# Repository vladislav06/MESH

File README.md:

# DSAN
Distributed Sensor Actuator Network

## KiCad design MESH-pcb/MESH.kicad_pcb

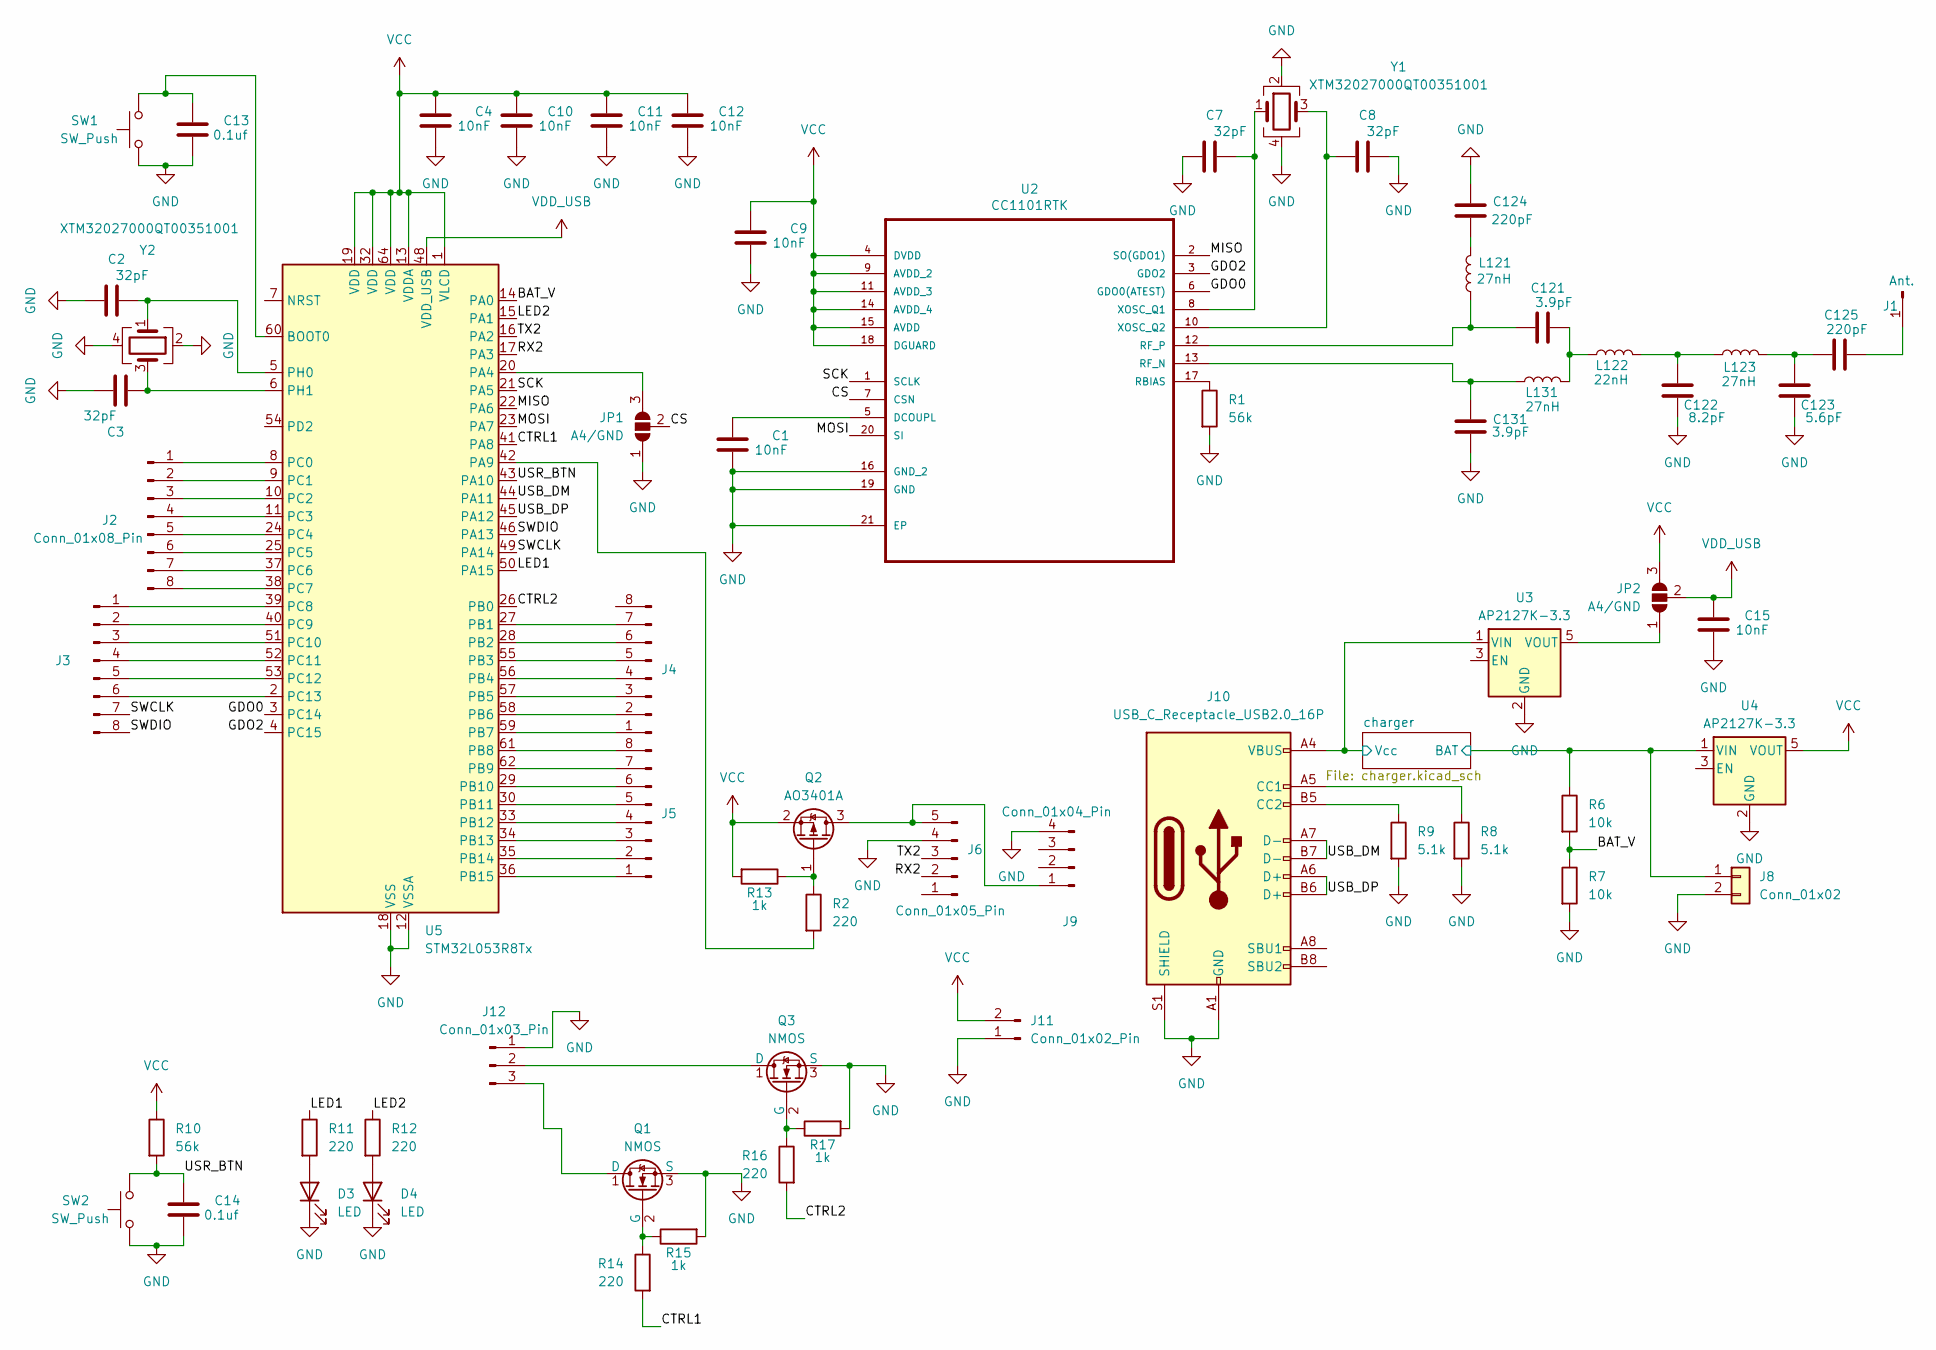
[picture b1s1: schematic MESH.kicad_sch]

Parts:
C1, C4, C9, C10, C11, C12, C15: 10nF; C_0402_1005Metric
C2, C3, C7, C8: 32pF; C_0402_1005Metric
C13, C14: 0.1uf; C_0402_1005Metric
C121, C131: 3.9pF; C_0402_1005Metric
C122: 8.2pF; C_0402_1005Metric
C123: 5.6pF; C_0402_1005Metric
C124, C125: 220pF; C_0402_1005Metric
D3, D4: LED; LED_0603_1608Metric_Pad1.05x0.95mm_HandSolder
J1: Ant.; PinHeader_1x01_P1.00mm_Vertical
J2, J3, J4, J5: Conn_01x08_Pin; PinHeader_1x08_P2.54mm_Bare
J6: Conn_01x05_Pin; PinHeader_1x05_P1.00mm_Vertical
J8: Conn_01x02; PinHeader_1x02_P2.54mm_Vertical
J9: Conn_01x04_Pin; PinHeader_1x04_P2.00mm_Vertical
J10: USB_C_Receptacle_USB2.0_16P; USB_C_Receptacle_Palconn_UTC16-G
J11: Conn_01x02_Pin; PinHeader_1x02_P2.54mm_Bare
J12: Conn_01x03_Pin; PinHeader_1x03_P2.54mm_Bare
JP1, JP2: A4/GND; SolderJumper-3_P2.0mm_Open_TrianglePad1.0x1.5mm_NumberLabels
L121, L123, L131: 27nH; L_0402_1005Metric
L122: 22nH; L_0402_1005Metric
Q1, Q3: NMOS; SOIC127P600X175-8N
Q2: AO3401A; SOT-23
R1, R10: 56k; R_0201_0603Metric_Pad0.64x0.40mm_HandSolder
R2, R11, R12, R14, R16: 220; R_0201_0603Metric_Pad0.64x0.40mm_HandSolder
R6, R7: 10k; R_0201_0603Metric_Pad0.64x0.40mm_HandSolder
R8, R9: 5.1k; R_0201_0603Metric_Pad0.64x0.40mm_HandSolder
R13, R15, R17: 1k; R_0201_0603Metric_Pad0.64x0.40mm_HandSolder
SW1, SW2: SW_Push; SW_5.6_3.1
U2: CC1101RTK; QFN-20-1EP_4x4mm_P0.5mm_EP2.5x2.5mm
U3, U4: AP2127K-3.3; SOT-23-5
U5: STM32L053R8Tx; LQFP-64_10x10mm_P0.5mm
Y1, Y2: XTM32027000QT00351001; Crystal_SMD_3225-4Pin_3.2x2.5mm_HandSoldering

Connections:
/BAT_V: R6.2, R7.1, U5.14 (PA0)
/CS: JP1.2 (C), U2.7 (CSN)
/CTRL1: R14.2, U5.41 (PA8)
/CTRL2: R16.2, U5.26 (PB0)
/GDO0: U2.6 (GDO0(ATEST)), U5.3 (PC14)
/GDO2: U2.3 (GDO2), U5.4 (PC15)
/LED1: R11.1, U5.50 (PA15)
/LED2: R12.1, U5.15 (PA1)
/MISO: U2.2 (SO(GDO1)), U5.22 (PA6)
/MOSI: U2.20 (SI), U5.23 (PA7)
/RX2: J6.2, U5.17 (PA3)
/SCK: U2.1 (SCLK), U5.21 (PA5)
/SWCLK: J3.7, U5.49 (PA14)
/SWDIO: J3.8, U5.46 (PA13)
/TX2: J6.3, U5.16 (PA2)
/USB_DM: J10.A7 (D-), J10.B7 (D-), U5.44 (PA11)
/USB_DP: J10.A6 (D+), J10.B6 (D+), U5.45 (PA12)
/USR_BTN: C14.1, R10.2, SW2.2, U5.43 (PA10)
/charger/BAT: J8.1, R6.1, U4.1 (VIN); also elsewhere on the board
/charger/Vcc: J10.A4 (VBUS), J10.A9 (VBUS), J10.B4 (VBUS), J10.B9 (VBUS), U3.1 (VIN); also elsewhere on the board
GND: C1.2, C2.1, C3.2, C4.2, C7.1, C8.2, C9.2, C10.2, C11.2, C12.2, C13.2, C14.2, C15.2, C122.2, C123.2, C124.1, C131.2, D3.1 (K), D4.1 (K), J6.4, J8.2, J9.4, J10.A1 (GND), J10.A12 (GND), J10.B1 (GND), J10.B12 (GND), J10.S1 (SHIELD), J11.1, J12.1, JP1.1 (A), Q1.3 (S), Q3.3 (S), R1.2, R7.2, R8.2, R9.2, R15.2, R17.2, SW1.1, SW2.1, U2.16 (GND_2), U2.19 (GND), U2.21 (EP), U3.2 (GND), U4.2 (GND), U5.12 (VSSA), U5.18 (VSS), U5.31 (VSS), U5.47 (VSS), U5.63 (VSS), Y1.2, Y1.4, Y2.2, Y2.4; also elsewhere on the board
unnamed: C121.2, L122.1, L131.2
unnamed: C122.1, L122.2, L123.1
unnamed: C123.1, C125.1, L123.2
unnamed: C124.2, L121.2
unnamed: D3.2 (A), R11.2
unnamed: D4.2 (A), R12.2
unnamed: C125.2, J1.1
unnamed: J2.1, U5.8 (PC0)
unnamed: J2.2, U5.9 (PC1)
unnamed: J2.3, U5.10 (PC2)
unnamed: J2.4, U5.11 (PC3)
unnamed: J2.5, U5.24 (PC4)
unnamed: J2.6, U5.25 (PC5)
unnamed: J2.7, U5.37 (PC6)
unnamed: J2.8, U5.38 (PC7)
unnamed: J3.1, U5.39 (PC8)
unnamed: J3.2, U5.40 (PC9)
unnamed: J3.3, U5.51 (PC10)
unnamed: J3.4, U5.52 (PC11)
unnamed: J3.5, U5.53 (PC12)
unnamed: J3.6, U5.2 (PC13)
unnamed: J4.1, U5.59 (PB7)
unnamed: J4.2, U5.58 (PB6)
unnamed: J4.3, U5.57 (PB5)
unnamed: J4.4, U5.56 (PB4)
unnamed: J4.5, U5.55 (PB3)
unnamed: J4.6, U5.28 (PB2)
unnamed: J4.7, U5.27 (PB1)
unnamed: J5.1, U5.36 (PB15)
unnamed: J5.2, U5.35 (PB14)
unnamed: J5.3, U5.34 (PB13)
unnamed: J5.4, U5.33 (PB12)
unnamed: J5.5, U5.30 (PB11)
unnamed: J5.6, U5.29 (PB10)
unnamed: J5.7, U5.62 (PB9)
unnamed: J5.8, U5.61 (PB8)
unnamed: J6.5, J9.1, Q2.3 (D)
unnamed: J10.A5 (CC1), R8.1
unnamed: J10.B5 (CC2), R9.1
unnamed: J12.2, Q3.1 (D)
unnamed: J12.3, Q1.1 (D)
unnamed: JP1.3 (B), U5.20 (PA4)
unnamed: JP2.1 (A), U3.5 (VOUT)
unnamed: Q1.2 (G), R14.1, R15.1
unnamed: Q2.1 (G), R2.1, R13.1
unnamed: Q3.2 (G), R16.1, R17.1
unnamed: C1.1, U2.5 (DCOUPL)
unnamed: R1.1, U2.17 (RBIAS)
unnamed: C131.1, L131.1, U2.13 (RF_N)
unnamed: C121.1, L121.1, U2.12 (RF_P)
unnamed: C7.2, U2.8 (XOSC_Q1), Y1.1
unnamed: C8.1, U2.10 (XOSC_Q2), Y1.3
unnamed: C13.1, SW1.2, U5.60 (BOOT0)
unnamed: R2.2, U5.42 (PA9)
unnamed: C2.2, U5.5 (PH0), Y2.1
unnamed: C3.1, U5.6 (PH1), Y2.3
VCC: C4.1, C9.1, C10.1, C11.1, C12.1, J11.2, JP2.3 (B), Q2.2 (S), R10.1, R13.2, U2.4 (DVDD), U2.9 (AVDD_2), U2.11 (AVDD_3), U2.14 (AVDD_4), U2.15 (AVDD), U2.18 (DGUARD), U4.5 (VOUT), U5.1 (VLCD), U5.13 (VDDA), U5.19 (VDD), U5.32 (VDD), U5.64 (VDD)
VDD_USB: C15.1, JP2.2 (C), U5.48 (VDD_USB)

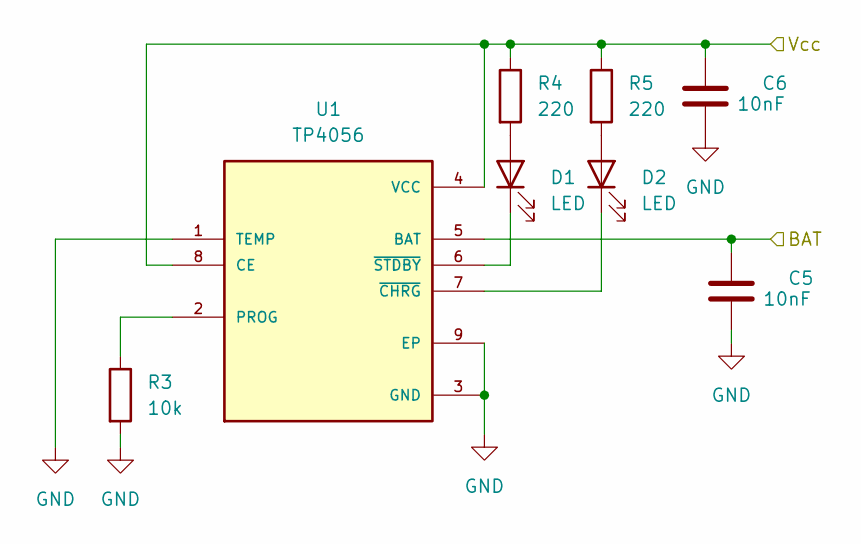
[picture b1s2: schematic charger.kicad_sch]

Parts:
C5, C6: 10nF; C_0402_1005Metric
D1, D2: LED; LED_0603_1608Metric_Pad1.05x0.95mm_HandSolder
R3: 10k; R_0201_0603Metric_Pad0.64x0.40mm_HandSolder
R4, R5: 220; R_0201_0603Metric_Pad0.64x0.40mm_HandSolder
U1: TP4056; SOP127P600X175-9N

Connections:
/charger/BAT: C5.1, U1.5 (BAT); also elsewhere on the board
/charger/Vcc: C6.1, R4.1, R5.1, U1.4 (VCC), U1.8 (CE); also elsewhere on the board
GND: C5.2, C6.2, R3.2, U1.1 (TEMP), U1.3 (GND), U1.9 (EP); also elsewhere on the board
unnamed: D1.2 (A), R4.2
unnamed: D1.1 (K), U1.6 (~STDBY)
unnamed: D2.2 (A), R5.2
unnamed: D2.1 (K), U1.7 (~CHRG)
unnamed: R3.1, U1.2 (PROG)

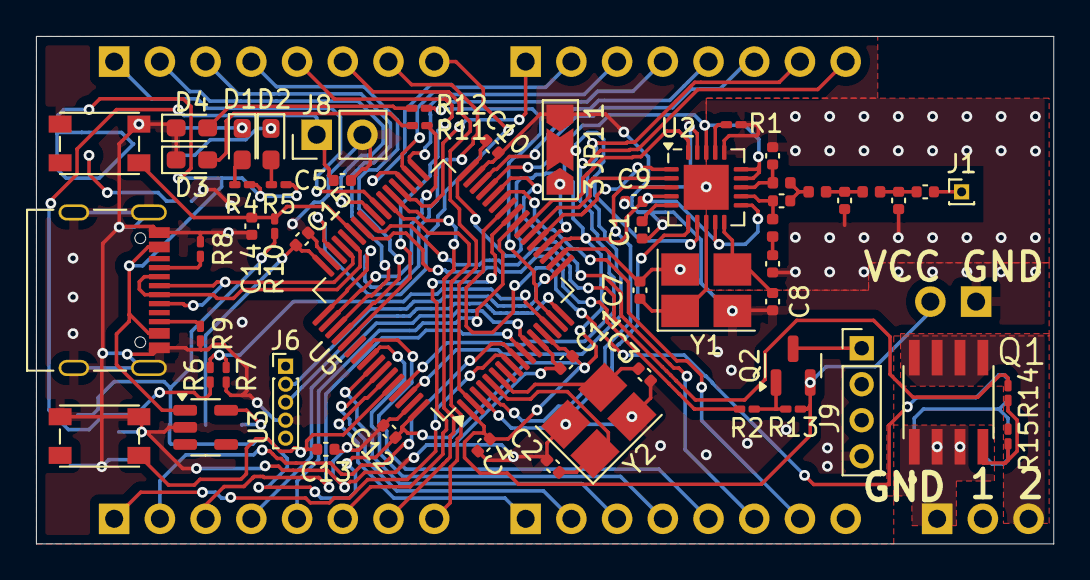
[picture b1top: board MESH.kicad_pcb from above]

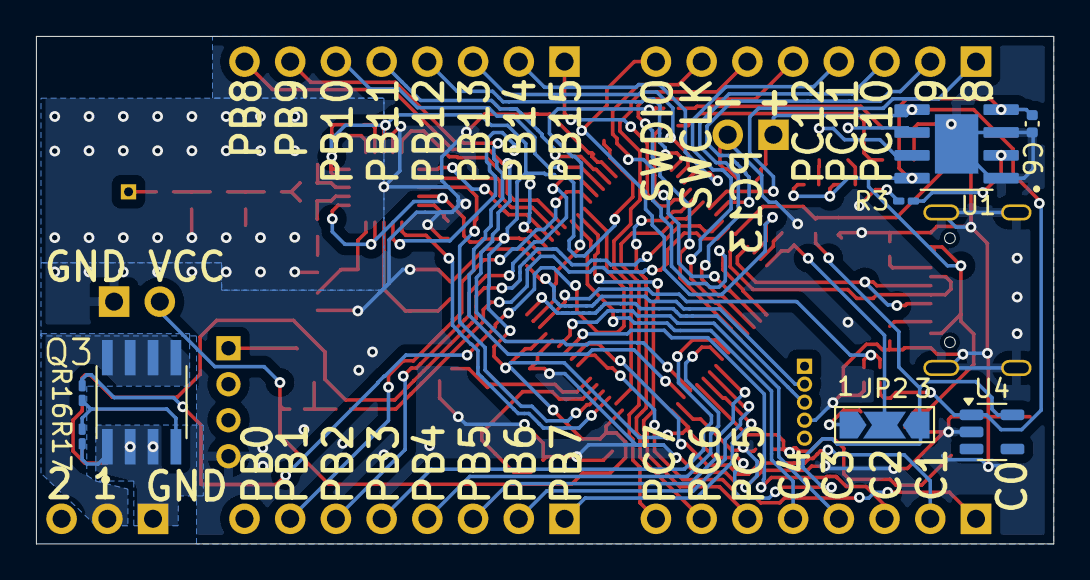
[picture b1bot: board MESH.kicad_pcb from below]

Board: 2 copper layers, 56.5 x 28.2 mm, 71 parts (8 on the bottom side), 84 nets.

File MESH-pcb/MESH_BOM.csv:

Reference,Value,Datasheet,Footprint,Qty,partnum
"C1,C4,C5,C6,C9,C10,C11,C12,C15",10nF,~,Capacitor_SMD:C_0402_1005Metric,9,C60133
"C2,C3,C7,C8",32pF,~,Capacitor_SMD:C_0402_1005Metric,4,C466228
"C13,C14",0.1uf,~,Capacitor_SMD:C_0402_1005Metric,2,C6119867
"C121,C131",3.9pF,~,Capacitor_SMD:C_0402_1005Metric,2,C41361089
C122,8.2pF,~,Capacitor_SMD:C_0402_1005Metric,1,C41361101
C123,5.6pF,~,Capacitor_SMD:C_0402_1005Metric,1,C41361095
"C124,C125",220pF,~,Capacitor_SMD:C_0402_1005Metric,2,C7503514
"D1,D2,D3,D4",LED,~,LED_SMD:LED_0603_1608Metric_Pad1.05x0.95mm_HandSolder,4,
J10,USB_C_Receptacle_USB2.0_16P,https://www.usb.org/sites/default/files/documents/usb_type-c.zip,Connector_USB:USB_C_Receptacle_Palconn_UTC16-G,1,C2927039
"L121,L123,L131",27nH,~,Inductor_SMD:L_0402_1005Metric,3,C391309
L122,22nH,~,Inductor_SMD:L_0402_1005Metric,1,C395059
Q2,AO3401A,http://www.aosmd.com/pdfs/datasheet/AO3401A.pdf,Package_TO_SOT_SMD:SOT-23,1,C5380686
"R1,R10",56k,~,Capacitor_SMD:C_0201_0603Metric_Pad0.64x0.40mm_HandSolder,2,C295859
"SW1,SW2",SW_Push,~,custom:SW_5.6_3.1,2,C2888428
U1,TP4056,,lib:SOP127P600X175-9N,1,C22451416
U2,CC1101RTK,1555264,Package_DFN_QFN:QFN-20-1EP_4x4mm_P0.5mm_EP2.5x2.5mm,1,C29953
"U4,U6",AP2127R-3.3,https://www.diodes.com/assets/Datasheets/AP2127.pdf,Package_TO_SOT_SMD:SOT-89-3,2,C156285
U5,STM32L053R8Tx,https://www.st.com/resource/en/datasheet/stm32l053r8.pdf,Package_QFP:LQFP-64_10x10mm_P0.5mm,1,C79207
"Y1,Y2",XTM32027000QT00351001,~,Crystal:Crystal_SMD_3225-4Pin_3.2x2.5mm_HandSoldering,1,C37635382

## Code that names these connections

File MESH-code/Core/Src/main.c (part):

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  /*Configure GPIO pin Output Level */
  HAL_GPIO_WritePin(GPIOB, GPIO_PIN_0|GPIO_PIN_12|GPIO_PIN_13, GPIO_PIN_RESET);

  /*Configure GPIO pins : PC13 PC1 PC3 PC5
                           PC7 PC8 PC9 PC10
                           PC11 PC12 */
  GPIO_InitStruct.Pin = GPIO_PIN_13|GPIO_PIN_1|GPIO_PIN_3|GPIO_PIN_5
                          |GPIO_PIN_7|GPIO_PIN_8|GPIO_PIN_9|GPIO_PIN_10
                          |GPIO_PIN_11|GPIO_PIN_12;
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  GPIO_InitStruct.Pull = GPIO_NOPULL;
  HAL_GPIO_Init(GPIOC, &GPIO_InitStruct);

  /*Configure GPIO pin : PC14 */
  GPIO_InitStruct.Pin = GPIO_PIN_14;
  GPIO_InitStruct.Mode = GPIO_MODE_IT_RISING;
  GPIO_InitStruct.Pull = GPIO_NOPULL;
  HAL_GPIO_Init(GPIOC, &GPIO_InitStruct);

  /*Configure GPIO pin : PC15 */
  GPIO_InitStruct.Pin = GPIO_PIN_15;
  GPIO_InitStruct.Mode = GPIO_MODE_IT_FALLING;
  GPIO_InitStruct.Pull = GPIO_NOPULL;
  HAL_GPIO_Init(GPIOC, &GPIO_InitStruct);

  /*Configure GPIO pins : PH0 PH1 */
  GPIO_InitStruct.Pin = GPIO_PIN_0|GPIO_PIN_1;
  GPIO_InitStruct.Mode = GPIO_MODE_ANALOG;
  GPIO_InitStruct.Pull = GPIO_NOPULL;
  HAL_GPIO_Init(GPIOH, &GPIO_InitStruct);

  /*Configure GPIO pins : PC0 PC2 PC4 PC6 */
  GPIO_InitStruct.Pin = GPIO_PIN_0|GPIO_PIN_2|GPIO_PIN_4|GPIO_PIN_6;
  GPIO_InitStruct.Mode = GPIO_MODE_OUTPUT_PP;
  GPIO_InitStruct.Pull = GPIO_NOPULL;
  GPIO_InitStruct.Speed = GPIO_SPEED_FREQ_LOW;
  HAL_GPIO_Init(GPIOC, &GPIO_InitStruct);

  /*Configure GPIO pins : PA1 PA4 PA8 PA9
                           PA15 */
  GPIO_InitStruct.Pin = GPIO_PIN_1|GPIO_PIN_4|GPIO_PIN_8|GPIO_PIN_9
                          |GPIO_PIN_15;
  GPIO_InitStruct.Mode = GPIO_MODE_OUTPUT_PP;
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  GPIO_InitStruct.Speed = GPIO_SPEED_FREQ_LOW;
  HAL_GPIO_Init(GPIOA, &GPIO_InitStruct);

  /*Configure GPIO pins : PB0 PB12 PB13 */
  GPIO_InitStruct.Pin = GPIO_PIN_0|GPIO_PIN_12|GPIO_PIN_13;
  GPIO_InitStruct.Mode = GPIO_MODE_OUTPUT_PP;
  GPIO_InitStruct.Pull = GPIO_NOPULL;
  GPIO_InitStruct.Speed = GPIO_SPEED_FREQ_LOW;
  HAL_GPIO_Init(GPIOB, &GPIO_InitStruct);

  /*Configure GPIO pins : PB2 PB10 PB11 PB14
                           PB15 PB3 PB4 PB5
                           PB6 PB7 PB8 PB9 */
  GPIO_InitStruct.Pin = GPIO_PIN_2|GPIO_PIN_10|GPIO_PIN_11|GPIO_PIN_14
                          |GPIO_PIN_15|GPIO_PIN_3|GPIO_PIN_4|GPIO_PIN_5
                          |GPIO_PIN_6|GPIO_PIN_7|GPIO_PIN_8|GPIO_PIN_9;
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  GPIO_InitStruct.Pull = GPIO_NOPULL;
  HAL_GPIO_Init(GPIOB, &GPIO_InitStruct);

  /*Configure GPIO pin : PA10 */
  GPIO_InitStruct.Pin = GPIO_PIN_10;
  GPIO_InitStruct.Mode = GPIO_MODE_INPUT;
  GPIO_InitStruct.Pull = GPIO_NOPULL;
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
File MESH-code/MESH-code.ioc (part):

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Mcu.Name=STM32L053R(6-8)Tx
Mcu.Package=LQFP64
Mcu.UserName=STM32L053R8Tx
PA0.Mode=IN0
PA0.Signal=ADC_IN0
PA1.Signal=GPIO_Output
PA10.Signal=GPIO_Input
PA11.Mode=Device
PA11.Signal=USB_DM
PA12.Mode=Device
PA12.Signal=USB_DP
PA13.Mode=Serial_Wire
PA13.Signal=SYS_SWDIO
PA14.Mode=Serial_Wire
PA14.Signal=SYS_SWCLK
PA15.Signal=GPIO_Output
PA2.Mode=Asynchronous
PA2.Signal=USART2_TX
PA3.Mode=Asynchronous
PA3.Signal=USART2_RX
PA4.Signal=GPIO_Output
PA5.Mode=Full_Duplex_Master
PA5.Signal=SPI1_SCK
PA6.Mode=Full_Duplex_Master
PA6.Signal=SPI1_MISO
PA7.Mode=Full_Duplex_Master
PA7.Signal=SPI1_MOSI
PA8.Signal=GPIO_Output
PA9.Signal=GPIO_Output
PB0.Signal=GPIO_Output
PB1.Signal=ADC_IN9
PB12.Signal=GPIO_Output
PB13.Signal=GPIO_Output
PC0.Signal=GPIO_Output
PC14-OSC32_IN.Signal=GPXTI14
PC15-OSC32_OUT.GPIOParameters=GPIO_ModeDefaultEXTI
PC15-OSC32_OUT.GPIO_ModeDefaultEXTI=GPIO_MODE_IT_FALLING
PC15-OSC32_OUT.Signal=GPXTI15
PC2.Signal=GPIO_Output
PC4.Signal=GPIO_Output
PC6.Signal=GPIO_Output
RCC.HSE_VALUE=8000000
RCC.SYSCLKFreq_VALUE=32000000
RCC.SYSCLKSource=RCC_SYSCLKSOURCE_PLLCLK
board=custom

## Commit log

2025-02-23 Schematic update, PCB routing update
2025-03-02 Added custom component library, Almost final component placement
2025-03-10 routing almost complete
2025-03-10 Ready to be exported
2025-03-17 added pinheader footprint without outline, added pin names to silkscreen
2025-03-17 Added all pin names
2025-03-19 pcb ordered
2025-04-06 MX project created Ported cc1101 driver from c++ to c Transition works
2025-04-07 Added espProg openocd configuration
2025-04-08 Separated transmitter and receiver functions, added id check
2025-04-09 Added new pin definitions, Added post generation script
2025-04-09 Added post generation script
2025-04-11 Added interrupt on pc14 and pc15
2025-04-11 Changed EXTI priority to 3 Added ability to receive packets through callback Added ability to receive long packets (up to 256 bytes)
2025-04-13 Added ability to transmit long packets asynchronously, async part of driver is ready
2025-04-14 Added ability to receive/transmit synchronously, inside receive interrupt
2025-04-17 moved to config struct
2025-05-01 Added ability to get current rssi value. Added test stuff.
2025-05-01 Added test stuff.
2025-05-01 Added hardware definition. Code cleanup.
2025-05-03 Hw fix
2025-05-03 Attempt to measure Time of Flight between 2 modules
2025-05-04 cc1101_measure_round_trip_responder responds only once
2025-05-07 Added ld2410b enable
2025-05-09 Added uart dma
2025-05-11 Added math expression parsing library Added reduced printf uart transmission fix
2025-05-14 base driver for ld2410b sensor
2025-05-14 Fixed utils Added forces ack handing to ld driver
2025-05-14 Added tiny printf and expr. Reduced usb buffer sizes
2025-05-14 repo fix
2025-05-16 enabled rng implemented fastest way to write to eeprom
2025-05-17 moved eeprom store into its own file
2025-05-25 added some comments
2025-05-26 Added packet definition Added routing table and routing functions Added receive handler Added actuator definition
2025-05-26 Routing fix cc driver fix, added timeout protection wireless communication further implementation
2025-05-30 Added discovery request and response packets and handling, still buggy
2025-05-30 Added CCA and listen before talk routing table print fix
2025-06-04 Implemented DRQ/DRS CSR ACK
2025-06-05 base driver for ld2410b sensor - incomplete, WIP
2025-06-06 Removed macro support from expr parser. Added some structures to configuration.h Added stack marking
2025-06-07 expr fixes added configurationLoader for loading configuration from usb
2025-06-07 Some serial communication tests
2025-06-07 functional ld2410b driver
2025-06-08 main method cleanup
2025-06-08 Added adc read support
2025-06-08 Added configuration to eeprom upload
2025-06-08 updated parser
2025-06-08 actuator load config, also fixes for ld2410b driver
2025-06-08 Added ability to send sensor data to all subscribed nodes
2025-06-08 Fixed algorith length parsing
2025-06-08 actuator handle cd function
2025-06-08 actuator expression evaluate function
2025-06-08 reorganization
2025-06-09 sensor init function declaration and implementation
2025-06-09 final fixes
2025-06-09 more fixes
2025-06-10 more fixes #2
2025-06-10 Added local configuration loader, custom sensor and actuator configuration metaLanguage
2025-06-10 bug fixes and renaming
2025-06-11 Added unsubscription More debug info New node added to sensor config
2025-06-11 Added min max and avg data mix modes
2025-06-28 Added poster image

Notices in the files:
MESH-code/Core/Src/main.c:
Copyright (c) 2025 STMicroelectronics.
All rights reserved.
This software is licensed under terms that can be found in the LICENSE file
